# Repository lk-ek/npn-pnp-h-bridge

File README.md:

# H-Bridge Driver for 3.3V PWM Input (HI/LO)

This project is a discrete transistor-based H-bridge driver designed to drive loads such as a bi-directional LED string or small DC motors (you *need* to populate the protection diodes in that case!) using two 3.3V logic-level PWM inputs.

Special thanks to [PCBWay.com](https://pcbway.com) for reaching out to supply me with prototype PCBs. They turned out amazing and do work like a charm! This gave me the opportunity to fix a few things I got wrong in the first version - especially adding the protection diodes so this circuit can now not only drive LED-strips with anti-parallel circuits, but also small DC motors.

Also, if you are looking for a tool to handle your PCBs while soldering, look no further - [eHaJo's LötDock](https://www.ehajo.de/products/lotdock-workshop-set-a5-lotdock-base-a5-lotdock-starterkit) is there to save you! It's awesome. See it in action for a minute [here](https://www.youtube.com/watch?v=5W0FboXXDTc) (timelapse of the assembly of this PCB).

## Overview

The circuit takes two complementary (non-overlapping) PWM inputs: `L_IN` and `R_IN`, each at 3.3V logic level. These signals are level-shifted and drive a discrete H-bridge output stage composed of NPN and PNP BJTs. The output connects to a load (e.g., LED strip) in a push-pull fashion.

## Inputs

- `L_IN`: 3.3V logic PWM input (controls left-side NPN-PNP transistors)
- `R_IN`: 3.3V logic PWM input (controls right-side NPN-PNP transistors)

⚠️ **Important:**  
`L_IN` and `R_IN` **must be phase-shifted**, even though the NPN-PNP-pair makes sure shoot-through is impossible. If both are high simultaneously, the output is off.

## Supply

- `VDD`: Power rail for the H-bridge (used to drive the load), probably up to 12V
- `GND`: Common ground

## Outputs

- `O1`, `O2`: Differential outputs to the load

## Notes

- Input resistors and capacitors are used for filtering and protection.
- BJTs are used in complementary pairs (NPN/PNP) for each half-bridge.
- The BAT54S dual-diodes serve as a baker clamp to help the BJTs switch faster and reduce shoot-through from 2-3us to 0.5us in the simulation
- So far, a one-sided load of 210mA worked fine without anything getting noticably warm. In theory, it should tolerate at least 250mA on each side of the H-Bridge, so at least 500mA in total, but this is so far untested.
- Load: connected between `O1` and `O2` (e.g., antiparallel LEDs or small DC motor)
- You can use [WLED](https://kno.wled.ge/) to drive the inputs - select "PWM CCT" as LED-type. For the phase-shifted PWM to work, you might need to use a beta version from [wled-install.github.io](https://wled-install.github.io/) - 0.16 nightly worked for me.  
- [ESPHome](https://esphome.io) works as well, see example below

```yaml
output:
  - platform: ledc
    id: pwm_l
    pin: 3
    frequency: 5kHz
    inverted: false
    phase_angle: 0.0

  - platform: ledc
    id: pwm_r
    pin: 4
    frequency: 5kHz
    inverted: false
    phase_angle: 180.0

  - platform: template
    id: pwm_bridge
    type: float
    write_action:
      lambda: |-
        float duty = clamp(state, 0.0f, 1.0f) * 0.5f;
        id(pwm_l).set_level(duty);
        id(pwm_r).set_level(duty);
        ESP_LOGD("custom", "H-Bridge Control: L=%.2f R=%.2f", duty, duty);
light:
  - platform: monochromatic
    name: "Bidirektionale Lampe"
    output: pwm_bridge

```

## Simulation

You can use KiCad's simulation tool to simulate the behaviour of this schematic. Modify the parameters of V1 and V2 to simulate different PWM patterns.

## Gerber files

You can download the gerber file directory as a zipfile and directly upload it to e.g. https://aisler.net, https://jlcpcb.com or https://pcbway.com

[Gerber file directory](production/npn-pnp-h-bridge)

## BOM

View [interactive BOM here](https://lk-ek.github.io/npn-pnp-h-bridge/)

| Designator         | Amount | Value   | Package |
|--------------------|--------|----------|----|
| C1, C2, C3, C4     | 4      | 100p     | 0805 
| C5                 | 1      | 100u     | 0805 
| D1, D2             | 2      | BAT54S Dual Schottky Diode | SOT-23 |
| D3, D4, D5, D6     | 4      | SS14 Schottky Diode | SMA |
| J1                 | 1      | JST S4B-PH-K-S | JST PH 2.0mm |
| J2                 | 1      | JST S2B-PH-K-S | JST PH 2.0mm |
| Q1, Q2             | 2      | MMDT3904 Dual NPN Package | SOT-363 |
| Ql1, Ql2           | 2      | BC327-25 | TO-92 |
| Qr1, Qr2           | 2      | BC337-40 | TO-92 |
| R1, R2, R5, R6, R11, R12    | 6      | 680      | 0805 |
| R3, R4             | 2      | 220k     | 0805 |
| R7, R10            | 2      | 4.7k       | 0805 |
| R8, R9             | 2      | 180 1/4W | 0805 |
| R13, R14           | 2      | 100 1/4W | 0805 |

## License

Attribution-NonCommercial-ShareAlike 4.0 International

See LICENSE for details, or: https://creativecommons.org/licenses/by-nc-sa/4.0/

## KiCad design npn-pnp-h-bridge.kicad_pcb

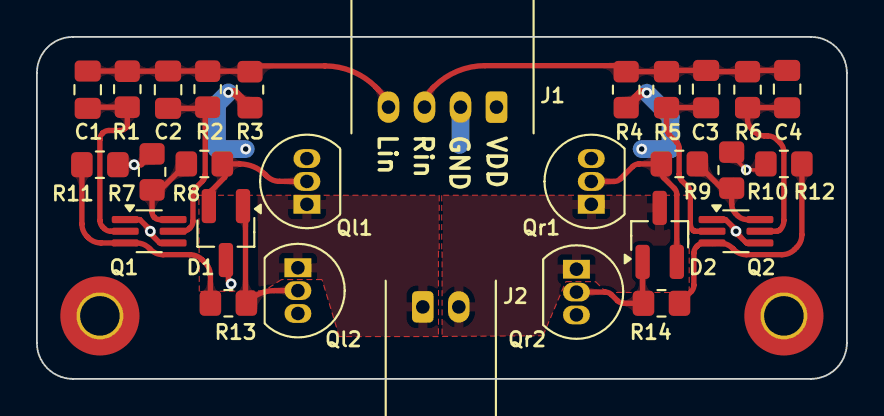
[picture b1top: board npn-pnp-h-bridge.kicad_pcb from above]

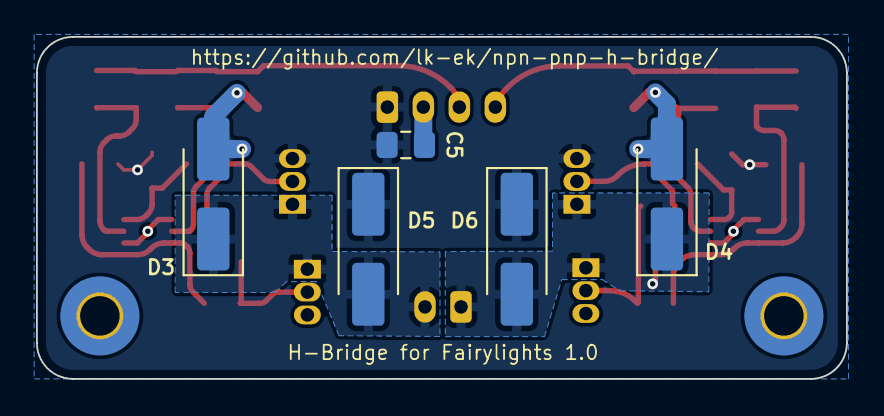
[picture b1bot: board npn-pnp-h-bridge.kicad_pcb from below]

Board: 4 copper layers, 45.0 x 19.0 mm, 35 parts (5 on the bottom side), 18 nets.

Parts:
C1, C2, C3, C4: 100p; C_0805_2012Metric_Pad1.18x1.45mm_HandSolder
C5: 100u; C_0805_2012Metric_Pad1.18x1.45mm_HandSolder
D1, D2: BAT54S; SOT-23_Handsoldering
D3, D4, D5, D6: SS14; D_SMA_Handsoldering
H1, H2: MountingHole_Pad; MountingHole_2.2mm_M2_Pad_TopBottom
J1: S4B-PH-K-S_LF__SN_; JST_PH_S4B-PH-K_1x04_P2.00mm_Horizontal
J2: S2B-PH-K-S_LF__SN_; JST_PH_S2B-PH-K_1x02_P2.00mm_Horizontal
Q1, Q2: MMDT3904; SOT-363_SC-70-6_Handsoldering
Ql1: BC327-25; TO-92_Inline
Ql2: BC337-40; TO-92_Inline
Qr1: BC327-25; TO-92_Inline
Qr2: BC337-40; TO-92_Inline
R1, R2, R5, R6: 680; R_0805_2012Metric_Pad1.20x1.40mm_HandSolder
R3, R4: 220k; R_0805_2012Metric_Pad1.20x1.40mm_HandSolder
R7, R10: 4.7k; R_0805_2012Metric_Pad1.20x1.40mm_HandSolder
R8, R9, R13, R14: 180; R_0805_2012Metric_Pad1.20x1.40mm_HandSolder
R11, R12: 2.2k; R_0805_2012Metric_Pad1.20x1.40mm_HandSolder

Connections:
/Hlb: D1.2 (K), Ql1.2 (B), R8.2 (-)
/Hrb: D2.2 (K), Qr1.2 (B), R9.1 (+)
/L_IN: C1.1 (+), C2.1 (+), J1.4, R1.1 (+), R2.1 (+), R3.2 (-)
/Llb: D1.1 (A), Ql2.2 (B), R13.2 (-)
/Lrb: D2.1 (A), Qr2.2 (B), R14.1 (+)
/O1: D1.3 (COM), D4.1 (K), D6.2 (A), J2.1, Ql1.1 (C), Ql2.1 (C)
/O2: D2.3 (COM), D3.1 (K), D5.2 (A), J2.2, Qr1.1 (C), Qr2.1 (C)
/R_IN: C3.1 (+), C4.1 (+), J1.3, R4.2 (-), R5.1 (+), R6.1 (+)
/bQ1: C2.2 (-), Q1.5 (B2), R2.2 (-)
/bQ2: C1.2 (-), Q1.2 (B1), R1.2 (-)
/bQ3: C4.2 (-), Q2.5 (B2), R6.2 (-)
/bQ4: C3.2 (-), Q2.2 (B1), R5.2 (-)
GND: C5.2 (-), D3.2 (A), D4.2 (A), H1.1, H2.1, J1.2, Q1.1 (E1), Q1.4 (E2), Q2.1 (E1), Q2.4 (E2), Ql2.3 (E), Qr2.3 (E), R3.1 (+), R4.1 (+)
unnamed: Q1.6 (C1), R7.1 (+), R8.1 (+)
unnamed: Q1.3 (C2), R11.1 (+), R13.1 (+)
unnamed: Q2.6 (C1), R9.2 (-), R10.1 (+)
unnamed: Q2.3 (C2), R12.1 (+), R14.2 (-)
VDD: C5.1 (+), D5.1 (K), D6.1 (K), J1.1, Ql1.3 (E), Qr1.3 (E), R7.2 (-), R10.2 (-), R11.2 (-), R12.2 (-)

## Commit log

2025-05-22 bd140-bd139
2025-05-22 remove lockfile
2025-05-22 dont know what im doing
2025-05-22 sort of working
2025-05-22 sorta working
2025-05-23 trying to reverse engineer original circuit
2025-05-23 first appearently working prototype
2025-05-23 change to bc807-40/817-40 and added mosfet to turn it all off
2025-07-12 fillet PCB and change transistor footprints
2025-07-12 fix missing workbook changes
2025-07-12 add README.md
2025-07-12 fix images
2025-07-12 add license
2025-07-12 add spice models
2025-07-12 add short BOM
2025-07-12 add package sizes to BOM
2025-07-12 replace images with current version; add schematic
2025-07-12 forgot to commit images
2025-07-12 layout changes
2025-07-12 Add simulation screenshot
2025-07-12 cosmetic updates
2025-07-12 add gerbers/fabrication output
2025-07-12 describe gerber download
2025-07-13 add WLED and ESPHome examples
2025-07-13 typo
2025-07-21 colorful nets
2025-08-07 add iBOM
2025-08-07 use github pages for ibom
2025-08-07 link to iBom page
2025-08-08 add optional freewheel diodes on the back layer
2025-08-08 update README for freewheel diodes
2025-08-08 add current gerbers and images
2025-08-08 missing image
2025-08-08 Thanks PCBWay for sponsoring prototypes of the new revision\!
2025-08-17 Alter resistor values to allow for higher O1/O2-current
2025-08-17 update bom
2025-08-22 Update README with current measurements; optimize resistor values for up to 500mA load
2025-08-22 update gerber files to current version
2025-08-22 Add image from circuit in action
2025-08-22 Add PCBWay sponsoring and eHaJos LötDock
2025-08-23 Make PCB stackable via 2x03 connheader
2025-08-24 add caps to gnd for the h-bridge bases
2025-08-24 tested with 210mA
2025-08-24 try adding a baker clamp
2025-08-24 finish Baker-Clamp circuit and PCB. Reduces shoot-through in simulations from 2us to 0.5us.
2025-08-24 add current images of baker-clamp version
2025-08-24 cleanups
2025-08-24 forgot C5 in BOM
2025-08-24 some small touchups
2025-08-24 Use handsoldering-footprints for diodes
2025-08-24 add baker clamp to README.md
2025-08-24 beautify schematic
2025-08-24 Changed MMBT3904 for a dual-NPN MMDT3904 for miniturization
2025-08-24 fine tuning
2025-08-24 more fine tuning; round board size
2025-08-26 final touches for dual-npn-package
2025-08-29 Add experimental and untested 3d model for a case
2025-08-31 pushed out the connectors to match the case
2025-09-07 Add 1.0 revision number, use current screenshots, add exported case
2025-09-09 simplified fairylights spice model
2025-09-10 changed some resistor values back to old values since the BJTs got very hot with lower pullups and lower base resistors
2025-09-10 update pcb with new values
2025-10-03 first 4-layer try
2025-10-07 finalize 4-layer design
